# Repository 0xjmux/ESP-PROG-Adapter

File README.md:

# ESP32 Firmware Debugging, as Easy as Possible

* [My blog post about this project](https://jacobbokor.com/posts/esp-jtag-adapter/)
* [Look ma, I was featured on Hackaday!](https://hackaday.com/2024/04/03/esp-prog-adapter-makes-your-esp32-tinkering-seamless/)

One of the things I've noticed in a lot of beginner ESP32 PCBs is a lack of hardware debugging interfaces, which is understandable since setting up JTAG can be a bit confusing when you're first exposed to it. This project's goal is to make using JTAG and connector-less footprints on your PCBs as easy and cheap as possible. 

#### To get started, all you need is: 
1. An ESP-Prog, Espressif's cheap and flexible UART and JTAG adapter - [Aliexpress, ~$11 US](https://s.click.aliexpress.com/e/_DnkCFmz)
1. SOIC-8 Clip programming cable for SOICbite - [Aliexpress, ~$3](https://www.aliexpress.us/item/3256805091794484.html)
1. My adapter PCB and [connectors](#Components) ordered from your favorite PCB house ([Gerbers found under releases](https://github.com/0xjmux/ESP-PROG-Adapter/releases)) - ~$6 with connectors
1. My Kicad library (found under [ESP-EZ-Debug-KicadLib/](./ESP-EZ-Debug-KicadLib)) to easily include connector-less footprints in your Kicad designs. 

## ESP-Prog Programming Cable Adapter

Simple PCB that sits on top of the ESP-Prog to use the SOICbite and Tag-Connect TC2050-IDC adapters to program and debug ESP-based projects.

I originally made this adapter because I was in need of a hardware debugging solution for my ESP-based projects, and was tired of the dupont wire mess I needed to connect my programming cable to my JTAG adapter. 
 
## Features
* Easily connect your TC-2050-IDC and SOICbite programming cables to the ESP-Prog for JTAG and UART programming. 
    * This enables you to easily integrate component-less programming footprints with your ESP-based projects (and anything else using UART).
* Includes reversible UART TX/RX so if you mess it up on your board, you can easily change it on the adapter!
* Onboard SOICBite "loopback" footprint with TX-RX pins connected, allowing you to easily confirm your adapter's UART is working. 
* Detailed [schematic](files/esp-prog-adapter-v1.3-sch.pdf) containing all info you might need about the adapter, and easy to use schematic symbols (see [jmux-kicad-things](https://github.com/0xjmux/jmux-kicad-things)) for using the connectors in your designs. 

> [!NOTE]
> Schematic, Gerbers, and all other files needed for production and assembly can be found attached to the latest [release!](https://github.com/0xjmux/ESP-PROG-Adapter/releases/latest)

<p align="center">

<br>SOICBite (left) and Tag-Connect (right) cables connected to target boards using the adapter
</p>

<p align="center">

<br>SOICBite UART loopback usage (left) and top view of adapter on ESP-Prog (right)
</p>

## How to Use
* To make using these in your projects as easy as possible, I've created a Kicad library under `ESP-EZ-Debug-KicadLib/`. 
* These schematic symbols follow the [standard pinouts](https://github.com/SimonMerrett/SOICbite/tree/master?tab=readme-ov-file#pin-assignment) for each connector and are designed to be as self-explanatory as possible. There's an image example of connector wiring below, along with `UsageExamples.kicad_sch` so you can directly copy and paste into your designs. 

> [!NOTE]
> For information on installing and using the Kicad library, see [ESP-EZ-Debug-KicadLib/README.md](ESP-EZ-Debug-KicadLib/)

<p align="center">
<br>
Examples of how to wire up each connector to an ESP32
</p>

#### Pinouts
* The SOICBite UART connector follows the [standard pinout](https://github.com/SimonMerrett/SOICbite/tree/master?tab=readme-ov-file#pin-assignment). There wasn't a JTAG pinout already, so [I contributed one](https://github.com/SimonMerrett/SOICbite/pull/26) - although as of April 2024 it hasn't been merged into the repo. Because it hasn't been merged in, here's a pinout table. 

| Pin | ESP8266     | JTAG |
| --- | ----------- | ---- |
| 1   | Vcc         | Vcc  |
| 2   | GPIO0       | TMS  |
| 3   | GPIO2       | TCK  |
| 4   | GND         | GND  |
| 5   | RX          | TDI  |
| 6   | TX          | TDO  |
| 7   | CH_PD       | RTCK |
| 8   | RST         | NRST |

#### Software: Setting up Debugging with ESP-IDF and VSCode
* [This configuration note for the ESP-IDF VSCode extension](https://github.com/espressif/vscode-esp-idf-extension/blob/master/docs/DEBUGGING.md) is very helpful for setting up the IDE for hardware debugging
* [Espressif's documentation page on JTAG debugging for the ESP32](https://docs.espressif.com/projects/esp-idf/en/latest/esp32/api-guides/jtag-debugging/index.html#how-it-works)

## Hardware Setup/Soldering
The board comes with optional swappable UART jumpers. If this feature is not needed, simply solder the two solderjumpers (JP5 & JP6) that connect UART normally. 

> [!IMPORTANT]
> You must either bridge the solderjumpers or install the pin headers. If you don't do either, the UART interface won't be connected. 

### Components

| Component                   | Purpose                 | LCSC Part # | Link                                                                                                                                                                                       |
|-----------------------------|-------------------------|-------------|--------------------------------------------------------------------------------------------------------------------------------------------------------------------------------------------|
| 2x5P 2.54mm Female Header | ESP-Prog JTAG           | C18723056   | [LCSC](https://www.lcsc.com/product-detail/Female-Headers_HanElectricity-2541FV-2x5P_C18723056.html)                                                                                       |
| 2x3P 2.54mm Female Header | ESP-Prog UART           | C18723054    | [LCSC](https://lcsc.com/product-detail/Female-Headers_HanElectricity-2541FV-2x3P_C18723054.html) |
| 2x5P 1.27mm IDC Header      | TC2050 Conector         | C2962228    | [LCSC](https://www.lcsc.com/product-detail/IDC-Connectors_XKB-Connectivity-X1270WV-2x05A-6TV01_C2962228.html)                                                                              |
| 2x4P 2.54mm IDC Header (x2)      | SOICBite Connector      | C17179451   | [LCSC](https://www.lcsc.com/product-detail/IDC-Connectors_HanElectricity-HY2541WV-N-2x4P_C17179451.html)                                                                                    (x2) |
| 2x3P 2.54mm M Pin Header    | Reversible UART Jumpers | C2935918    | [LCSC](https://www.lcsc.com/product-detail/Pin-Headers_DEALON-DZ254R-22-06-63_C2935918.html)                                                                                               |

<br/>
<p align="center" >
<br>
If you found the work I put into this valuable, I'd appreciate if you could buy me a coffee so I can continue devoting time to extensively documenting my projects like this. 
</p>

### Soldering Order
I recommend going from shortest to tallest components, starting on the top side of the PCB. This is a very approachable solder job since everything is THT, but when attaching the headers that connect to the ESP-PROG there is the potential to burn the plastic of the connectors already installed on the top. Here's the order I recommend attaching the components:

1. TC2050 IDC Socket
1. 2x3 Pin header and SOICbite socket(s)
1. Downward facing F pin headers that connect to ESP-PROG

## Versions
### V1.4 - Polishing it up
* All functionality confirmed working.
* PCB updated to clarify assembly and use (text enlarged, dual 1x3 headers for reversible UART changed to single 2x3P using custom symbol).
* Vdd for JTAG and UART disconnected from each other on adapter, allowing different voltage to be used for each.
* Connected nRST line of ESP-PROG (from UART header) to board RESET line on JTAG pinout with solderjumper.
* Default connected solderjumpers changed to default open for Reversible UART, since I anticipate it'll be more used than not. 

---

### V1.3 - Redesigned (Again)
* Added headers that allow you to easily reverse UART TX-RX in case it was mixed up on the board you're testing. Just cut the solderjumpers on the bottom of the board, add header pins to the top, and the direction is now easily changeable. The bolded text indicates the default direction. 
* Fix symbol and footprint orientation for SOICbite from 1.2. Removed the TC2050 UART connector.
* Added a SOICbite connector on the side of the board with TX-RX pins connected together, allowing you to test that the adapter & drivers are working correctly via UART loopback. 
* Added notes to the schematic to make pinouts clear for anyone reading it, so similar symbol/footprint orientation mistakes aren't made again.

---

### V1.2 - JTAG arrives!
* Added JTAG compatibility headers, extended size of board. 
* The time between designing and ordering this version was on the order of months. Once I ordered it, I realized I had mixed up the pin ordering on the footprints, and needed to modify the schematic. 
* SOICbite connector wasn't oriented right. 

---

## References
* This project was inspired by BrechtVE's very cool [Universal J-Link adapter](https://github.com/Fescron/universal-jlink-adapter), which I was originally planning on using. Segger's discontinuation of the J-Link EDU left me in search of other options since the EDU mini doesn't support the ESP's Xtensa LX7 architecture, which is how I landed on the ESP-Prog.

---

The goal here is to make the joy of firmware debugging as easy to approach as possible; if you have any suggestions, please feel free to open a PR. 

<br>
<p align="center">
<br>
</p>

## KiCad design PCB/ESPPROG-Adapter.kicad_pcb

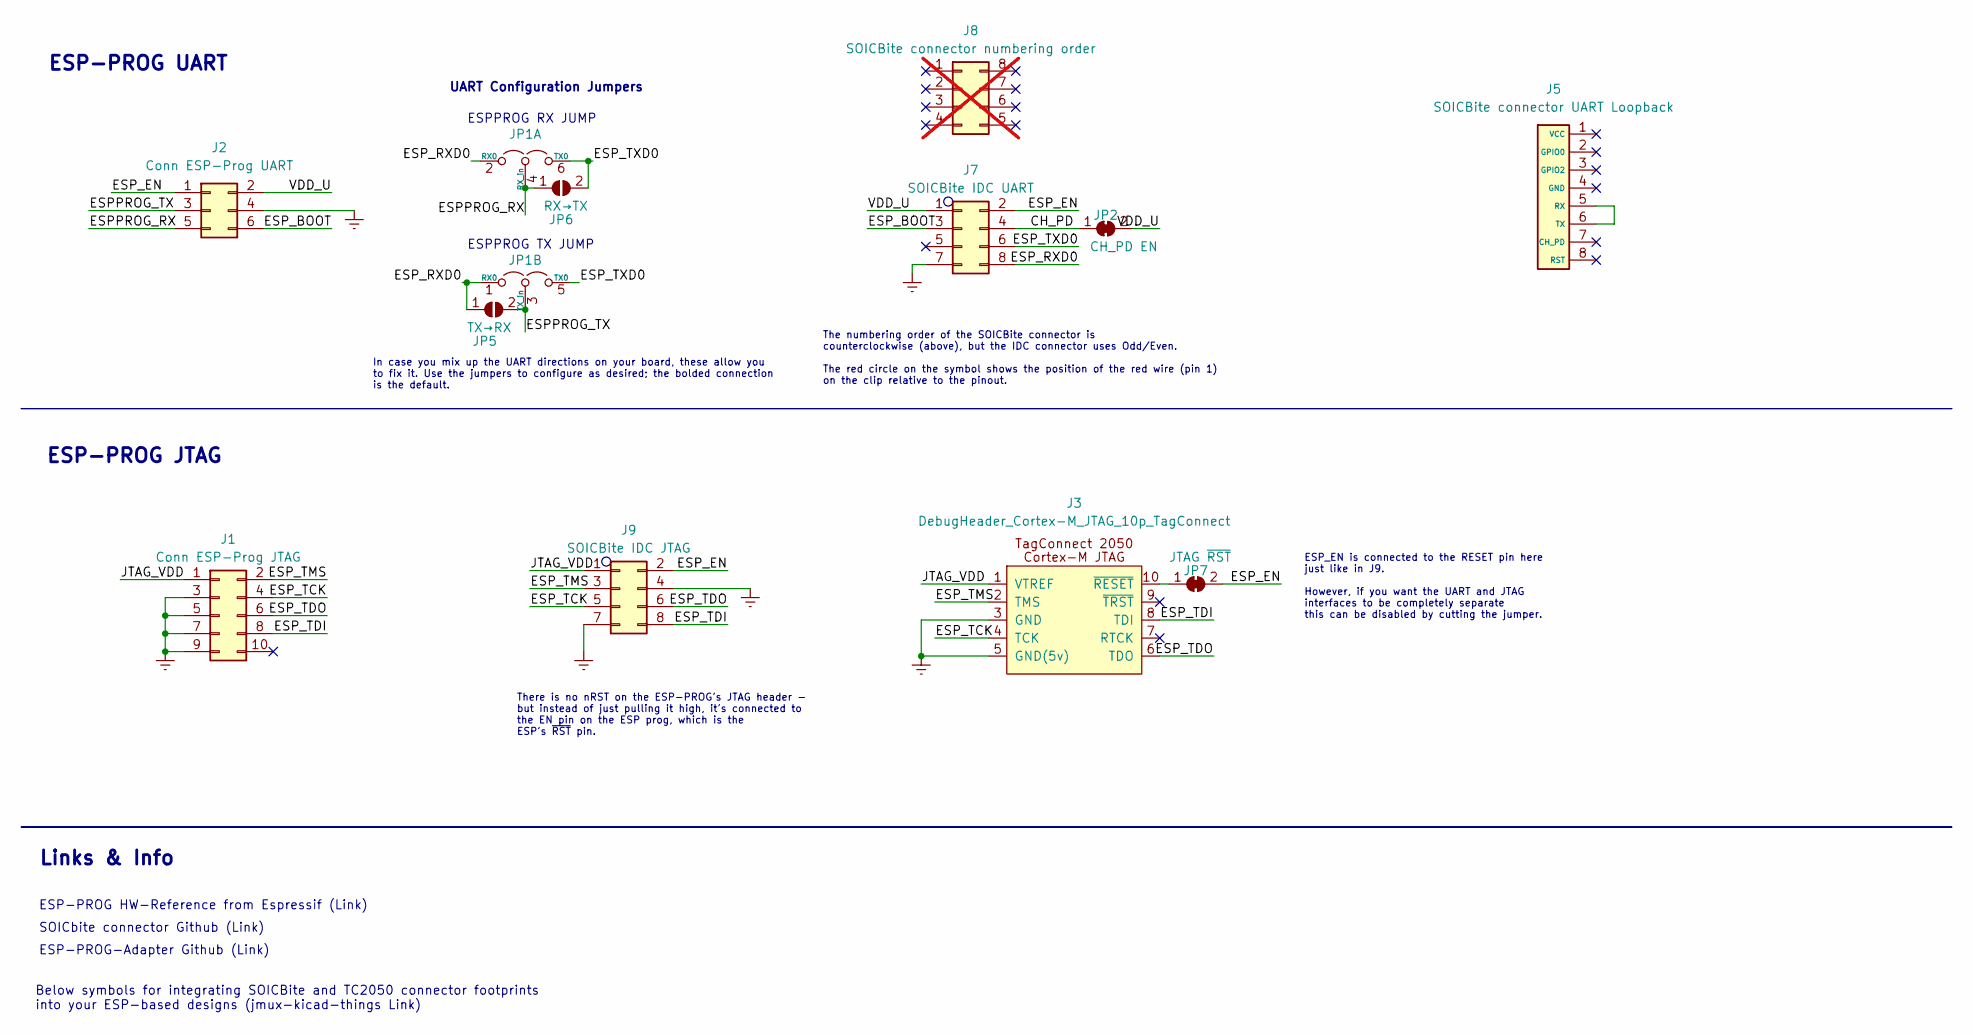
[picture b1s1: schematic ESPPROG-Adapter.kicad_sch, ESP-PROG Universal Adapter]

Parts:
J1: Conn ESP-Prog JTAG; PinSocket_2x05_P2.54mm_Vertical; LCSC C18723056
J2: Conn ESP-Prog UART; PinSocket_2x03_P2.54mm_Vertical; LCSC C5298392
J3: DebugHeader_Cortex-M_JTAG_10p_TagConnect; TC-2050-IDC-SOCKET; LCSC C2962228
J5: SOICBite connector UART Loopback; SOIC_clipProgSmall
J7: SOICBite IDC UART; IDC-Header_2x04_P2.54mm_Vertical; LCSC C17179451
J8: SOICBite connector numbering order; not fitted
J9: SOICBite IDC JTAG; IDC-Header_2x04_P2.54mm_Vertical; LCSC C17179451
JP1: ESPPROG_TX_RX_JUMP; PinHeader_2x03_P2.54mm_Vertical; LCSC C2935918
JP2: CH_PD EN; SolderJumper-2_P1.3mm_Bridged_RoundedPad1.0x1.5mm
JP5: TX→RX; SolderJumper-2_P1.3mm_Open_RoundedPad1.0x1.5mm
JP6: RX→TX; SolderJumper-2_P1.3mm_Open_RoundedPad1.0x1.5mm
JP7: JTAG ~{RST}; SolderJumper-2_P1.3mm_Bridged_RoundedPad1.0x1.5mm

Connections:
/CH_PD: J7.4, JP2.1 (A)
/ESPPROG_RX: J2.5, JP1.4 (RX_in), JP6.1 (A)
/ESPPROG_TX: J2.3, JP1.3 (TX_in), JP5.2 (B)
/ESP_BOOT: J2.6, J7.3
/ESP_EN: J2.1, J7.2, J9.2, JP7.2 (B)
/ESP_RXD0: J7.8, JP1.1 (RX0), JP1.2 (RX0), JP5.1 (A)
/ESP_TCK: J1.4, J3.4 (TCK), J9.5
/ESP_TDI: J1.8, J3.8 (TDI), J9.8
/ESP_TDO: J1.6, J3.6 (TDO), J9.6
/ESP_TMS: J1.2, J3.2 (TMS), J9.3
/ESP_TXD0: J7.6, JP1.5 (TX0), JP1.6 (TX0), JP6.2 (B)
/JTAG_VDD: J1.1, J3.1 (VTREF), J9.1
/VDD_U: J2.2, J7.1, JP2.2 (B)
Earth: J1.3, J1.5, J1.7, J1.9, J2.4, J3.3 (GND), J3.5 (GND(5v)), J7.7, J9.4, J9.7
unnamed: J3.10 (~RESET), JP7.1 (A)
unnamed: J5.5 (RX), J5.6 (TX)

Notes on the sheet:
UART Configuration Jumpers
ESP-PROG JTAG
SOICbite connector Github (Link)
ESP-PROG-Adapter Github (Link)
Below symbols for integrating SOICBite and TC2050 connector footprints into your ESP-based designs (jmux-kicad-things Link)
Links & Info
ESPPROG RX JUMP
ESP-PROG HW-Reference from Espressif (Link)
ESP-PROG UART
In case you mix up the UART directions on your board, these allow you to fix it. Use the jumpers to configure as desired; the bolded connection is the default.
There is no nRST on the ESP-PROG's JTAG header - but instead of just pulling it high, it's connected to the EN pin on the ESP prog, which is the ESP's ~{RST} pin.
The numbering order of the SOICBite connector is counterclockwise (above), but the IDC connector uses Odd/Even. The red circle on the symbol shows the position of the red wire (pin 1) on the clip relative to the pinout.
ESP_EN is connected to the RESET pin here just like in J9. However, if you want the UART and JTAG interfaces to be completely separate this can be disabled by cutting the jumper.
ESPPROG TX JUMP

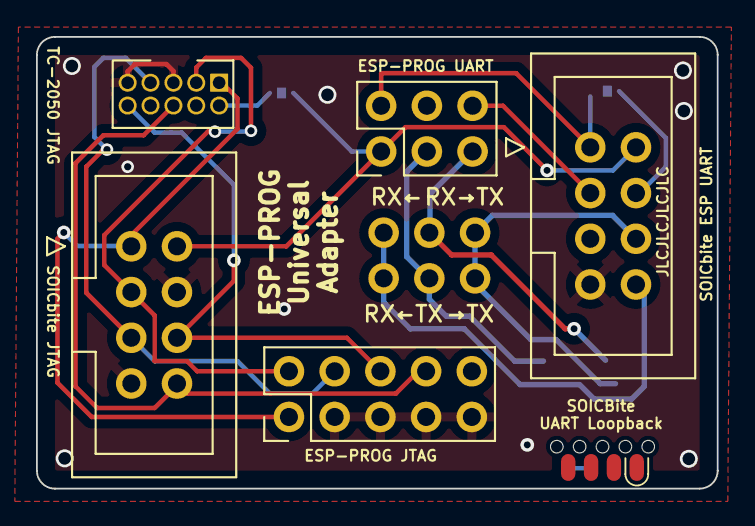
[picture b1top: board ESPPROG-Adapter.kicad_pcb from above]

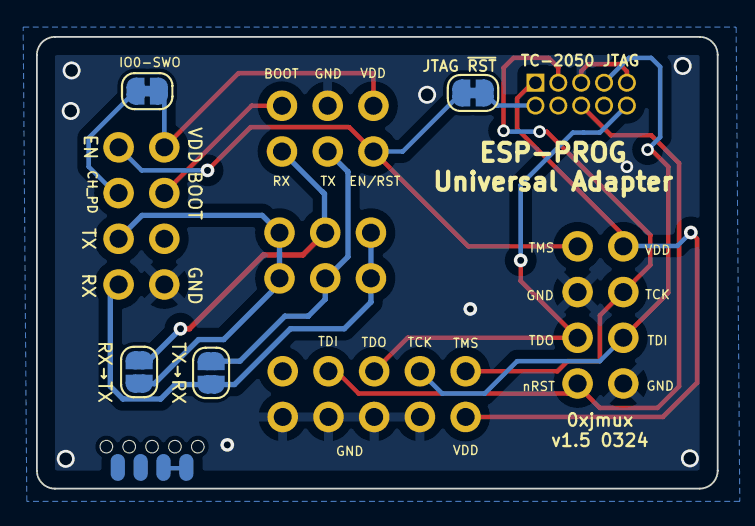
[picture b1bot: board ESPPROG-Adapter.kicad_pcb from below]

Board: 2 copper layers, 37.8 x 25.1 mm, 11 parts (5 on the bottom side), 16 nets.

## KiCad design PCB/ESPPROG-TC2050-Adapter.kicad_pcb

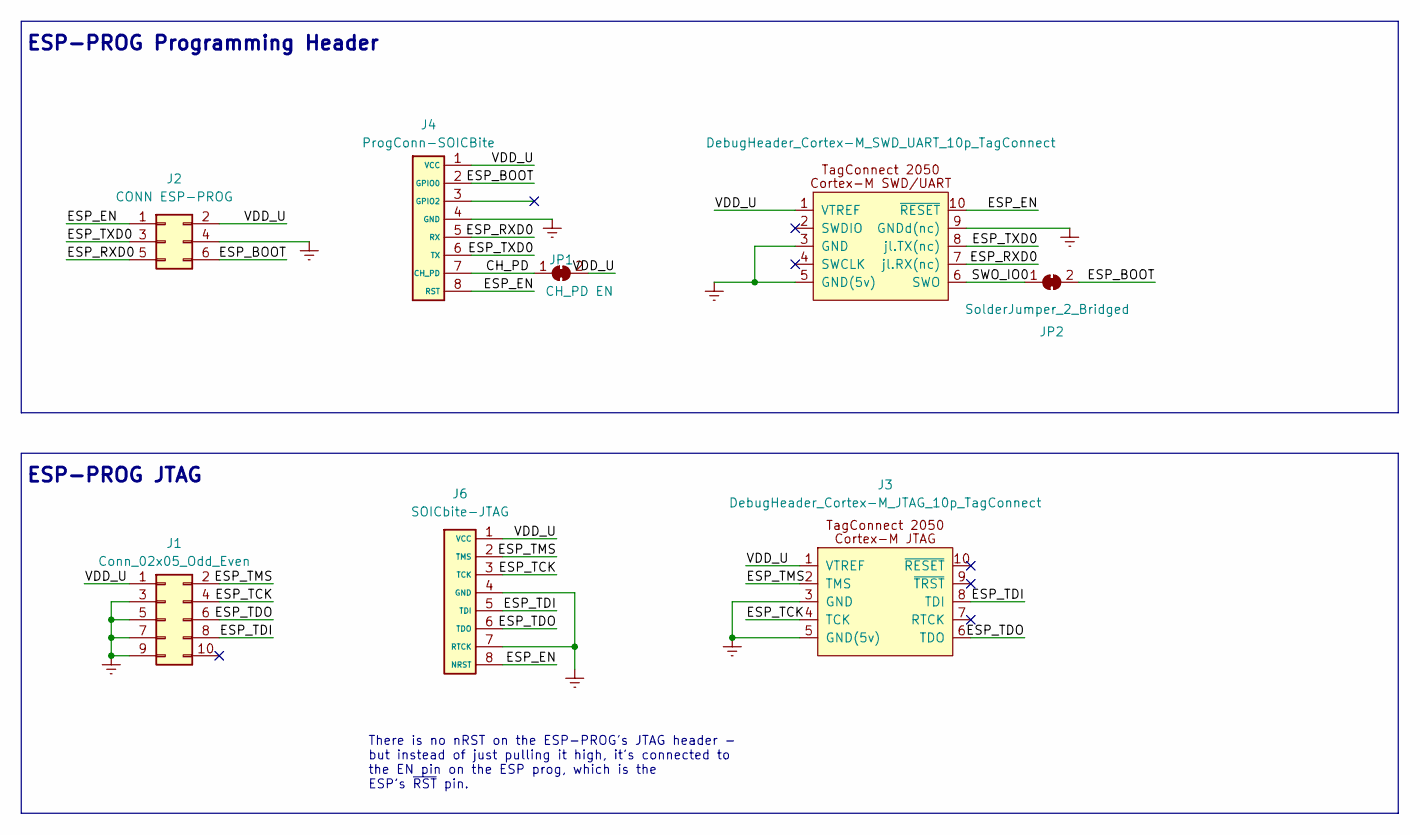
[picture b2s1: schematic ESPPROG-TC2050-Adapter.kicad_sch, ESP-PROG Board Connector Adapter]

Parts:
J1: Conn_02x05_Odd_Even; PinSocket_2x05_P2.54mm_Vertical
J2: CONN ESP-PROG; PinSocket_2x03_P2.54mm_Vertical; LCSC C5298392
J3: DebugHeader_Cortex-M_JTAG_10p_TagConnect; TC-2050-IDC-SOCKET; LCSC C2962228
J4: ProgConn-SOICBite; IDC-Header_2x04_P2.54mm_Vertical; LCSC C17179451
J5: DebugHeader_Cortex-M_SWD_UART_10p_TagConnect; TC-2050-IDC-SOCKET; LCSC C2962228
J6: SOICbite-JTAG; IDC-Header_2x04_P2.54mm_Vertical; LCSC C17179451
JP1: CH_PD EN; SolderJumper-2_P1.3mm_Bridged_RoundedPad1.0x1.5mm
JP2: SolderJumper_2_Bridged; SolderJumper-2_P1.3mm_Bridged_RoundedPad1.0x1.5mm

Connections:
/CH_PD: J4.7 (CH_PD), JP1.1 (A)
/ESP_BOOT: J2.6, J4.2 (GPIO0), JP2.2 (B)
/ESP_EN: J2.1, J4.8 (RST), J5.10 (~RESET), J6.8 (NRST)
/ESP_RXD0: J2.5, J4.5 (RX), J5.7 (jl.RX(nc))
/ESP_TCK: J1.4, J3.4 (TCK), J6.3 (TCK)
/ESP_TDI: J1.8, J3.8 (TDI), J6.5 (TDI)
/ESP_TDO: J1.6, J3.6 (TDO), J6.6 (TDO)
/ESP_TMS: J1.2, J3.2 (TMS), J6.2 (TMS)
/ESP_TXD0: J2.3, J4.6 (TX), J5.8 (jl.TX(nc))
/SWO_IO0: J5.6 (SWO), JP2.1 (A)
/VDD_U: J1.1, J2.2, J3.1 (VTREF), J4.1 (VCC), J5.1 (VTREF), J6.1 (VCC), JP1.2 (B)
Earth: J1.3, J1.5, J1.7, J1.9, J2.4, J3.3 (GND), J3.5 (GND(5v)), J4.4 (GND), J5.3 (GND), J5.5 (GND(5v)), J5.9 (GNDd(nc)), J6.4 (GND), J6.7 (RTCK)

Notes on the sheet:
ESP-PROG JTAG
ESP-PROG Programming Header
There is no nRST on the ESP-PROG's JTAG header - but instead of just pulling it high, it's connected to the EN pin on the ESP prog, which is the ESP's ~{RST} pin.

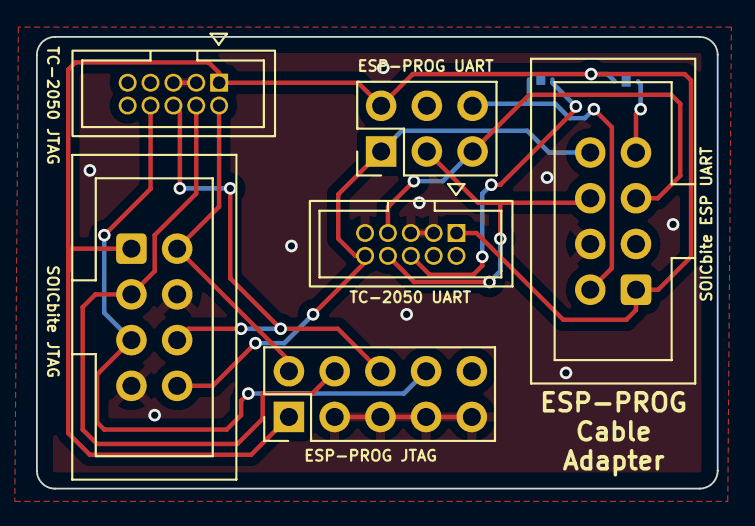
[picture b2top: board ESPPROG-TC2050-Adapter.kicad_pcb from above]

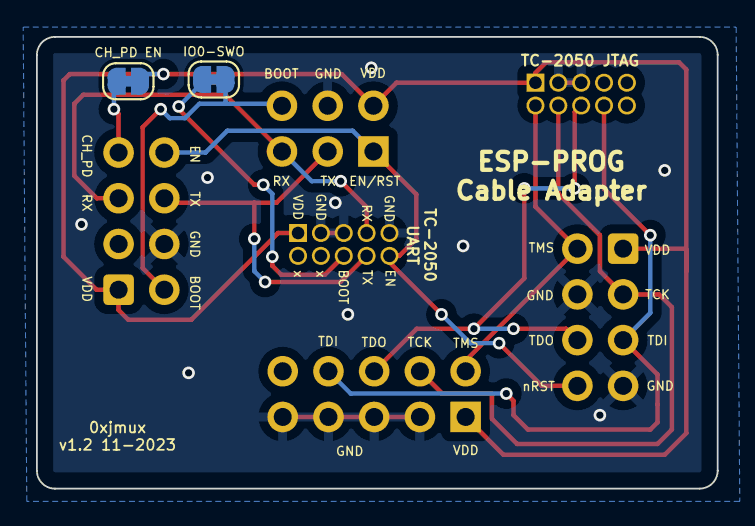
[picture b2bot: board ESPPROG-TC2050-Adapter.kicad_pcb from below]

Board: 2 copper layers, 37.8 x 25.1 mm, 8 parts (3 on the bottom side), 12 nets.

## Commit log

2023-11-06 initial commit and v1.0
2023-11-25 v1.0
2023-11-25 Majority of v1.1 changes
    * Removed card-edge connector
    * Added SOICbite 2x4P 2.54mm header with ESP8266 pinout
    * changed TC-2050 pinout to more default UART one
    * changed board dimensions to better fit on top of ESP-PROG
    * added to-scale picture of ESP-PROG in background to get better feel
    for alignment
2023-11-25 updated BOM fields and added LCSC PNs
2023-11-25 Redesign for v1.2
    * Added second F header to connect to ESP-PROG's JTAG header
    * added connectors for TC2050 and SOICbite for JTAG
    * had to extend board length as a result
2023-11-25 reorganized repo and added accompanying files
2023-11-25 Added readme and basic description
2023-11-25 added clarification
2024-01-31 nothing major, just a complete redesign for v1.3
2024-02-05 updated readme for v1.3 and added sch to files
2024-02-05 final readme change before v1.3
2024-02-05 readme update
2024-02-20 Writeup and minor changes for v1.4
    v1.3 arrived and all functionality was confirmed working. This commit
    adds the writeup, license, and some small modifications to the PCB to
    make it a little easier to use.
    * PCB updated to clarify assembly and use (text enlarged, dual 1x3 headers for reversible UART changed to single 2x3P using custom symbol).
    * Vdd for JTAG and UART disconnected from each other on adapter, allowing different voltage to be used for each.
    * Connected nRST line of ESP-PROG (from UART header) to board RESET line on JTAG pinout with solderjumper.
2024-02-20 Small revisions, image resizing in README
2024-02-20 Fix image sizing
2024-02-20 writing clarification in README and some formatting
2024-02-23 added Project Library with Symbols, updated README
2024-02-23 Minor README updates and formatting
2024-03-14 README updates, library renamed, readability updates on board
2024-03-31 v1.5 TC2050 pinout change
2024-04-04 Clarification and new example added to SCH, links in library updated
    * added link to hackaday article
    * added clarification about CH_PD and GPIO2 to SCH
    * Added example of ESP32 UART to SCH
    * Added pinout table to README
    * Updated example schematic
    * replaced connector wiring example png with updated version
2025-07-26 Fix part number and link of "2x3P Female Header"
    Fixes #1

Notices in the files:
README.md:
License: CERN OHL v2
